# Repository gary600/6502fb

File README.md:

# 6502 Framebuffer
A 160 by 120 pixel, 256-color framebuffer and VGA generator for a 6502-based computer, made
for CMU 98-341 Build Your Own Breadboard Computer.

Heavily inspired by Ben Eater's "[world's worst video
card](https://www.youtube.com/watch?v=l7rce6IQDWs)" saga, but with many
improvements:
- better timing compliance (shorter critical path -> no vertical artifacts)
- FFs instead of latches (easier to debug timing)
- higher resolution (160x120 vs. 100x75), accomplished through memory banking
- more common VGA mode (640x480 vs. 800x600)
- double-bufferring (updates aren't restricted to blanking period)
- software blanking (show solid black or white without drawing to every pixel)
- configurability (disable NMI if not needed)

This repo contains the KiCad files for the board, a corresponding Verilog
design and testbench, and a software simulator.

The board went through 2 revisions before it worked fully:

## Rev1
Revision 1 worked well enough to generate a valid VGA signal, but I made a major
mistake on the SRAM pinout which led to it not being able to interface with the
6502 computer. Another mistake: my minimum via diameter was too small, so it
cost like $40 extra...

However, despite these faults, I was able to bodge the row and column pins to
allow it to display an image from an EEPROM.

KiCad render

KiCad board view

 Part of the arduous debugging
process that eventually led to me discovering the SRAM mistake...

 It works! (with a static image...) The
EEPROM I used here has a much slower read speed than the SRAMs I designed for,
which leads to the vertial artifacts on some pixels here.

Closeup of Rev1 bodges: SRAMs removed and row/column signals routed to EEPROM + color routed in through header

## Rev2
Revision 2 fixed the pinout of the SRAM ICs, fixed the via size issue, added a
debug header for the config register, and added an optional 5V regulator that
can be used to power the entire computer.

KiCad render

KiCad board view

Final assembled board!

Power-on noise: this is expected! The SRAM does not have a deterministic state when powered on.

Drawing to the screen works!

And it can redraw live!

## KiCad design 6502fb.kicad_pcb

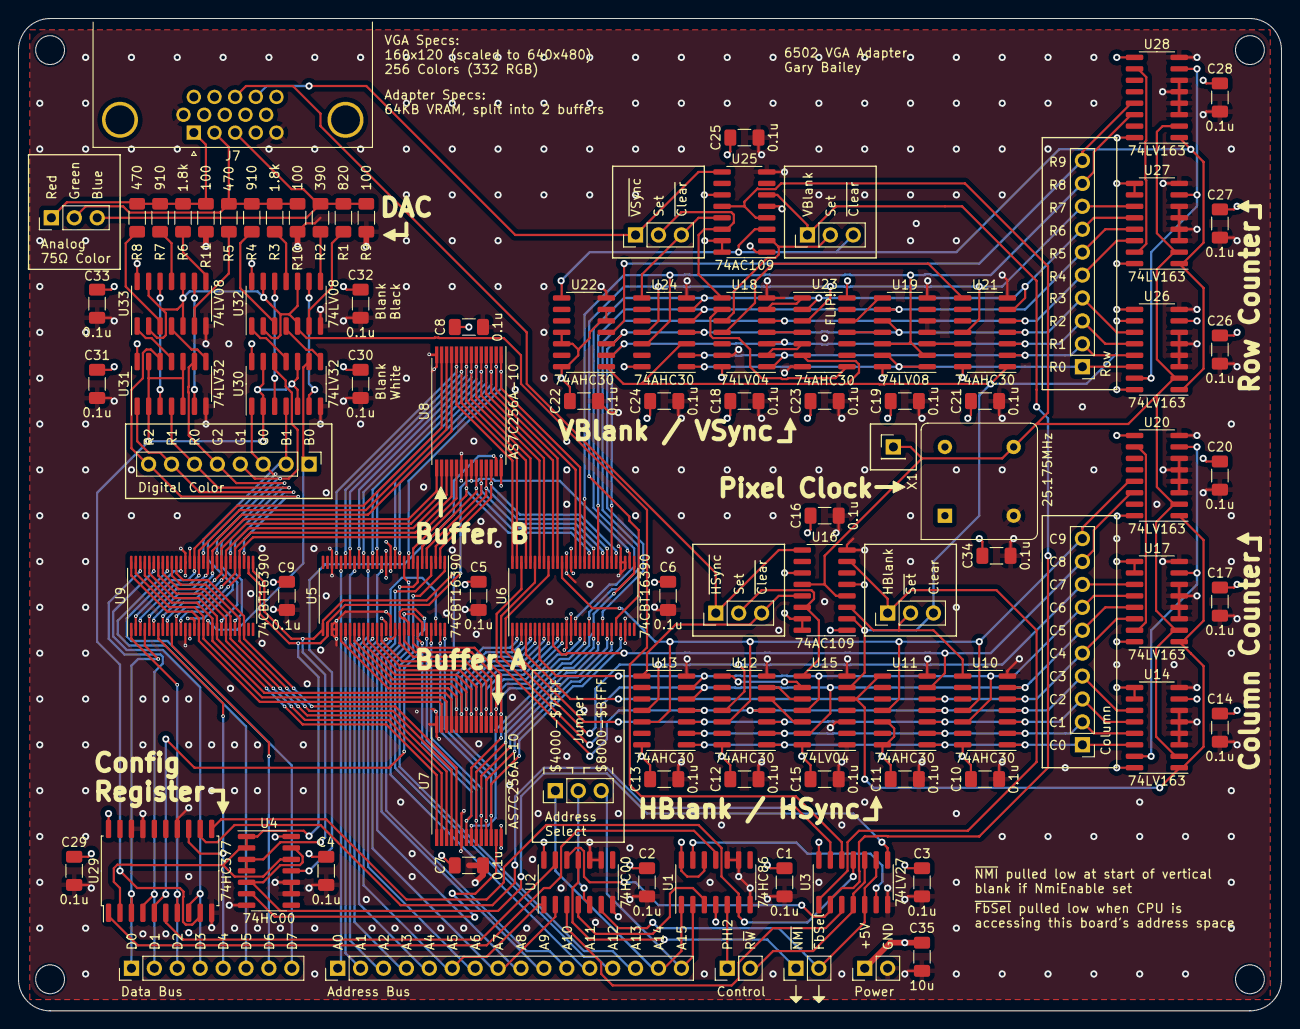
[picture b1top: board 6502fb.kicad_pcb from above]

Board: 4 copper layers, 140.0 x 110.0 mm, 100 parts (0 on the bottom side), 168 nets.

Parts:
C1, C2, C3, C4, C5, C6, C7, C8, C9, C10, C11, C12, C13, C14, C15, C16, C17, C18, C19, C20, C21, C22, C23, C24, C25, C26, C27, C28, C29, C30, C31, C32, C33, C34: 0.1u; C_1206_3216Metric_Pad1.33x1.80mm_HandSolder
C35: 10u; C_1206_3216Metric_Pad1.33x1.80mm_HandSolder
H1, H2, H3, H4: MountingHole; MountingHole_3.2mm_M3
J1, J3, J5: Conn_01x02; PinHeader_1x02_P2.54mm_Vertical
J2, J8: Conn_01x08; PinHeader_1x08_P2.54mm_Vertical
J4: Conn_01x16; PinHeader_1x16_P2.54mm_Vertical
J6, J11, J12, J13, J14, J15: Conn_01x03; PinHeader_1x03_P2.54mm_Vertical
J7: DE15_Receptacle_HighDensity; DSUB-15-HD_Female_Horizontal_P2.29x1.98mm_EdgePinOffset8.35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
J9, J10: Conn_01x10; PinHeader_1x10_P2.54mm_Vertical
J16: Conn_01x01; PinHeader_1x01_P2.54mm_Vertical
R1: 820; R_1206_3216Metric_Pad1.30x1.75mm_HandSolder
R2: 390; R_1206_3216Metric_Pad1.30x1.75mm_HandSolder
R3, R6: 1.8k; R_1206_3216Metric_Pad1.30x1.75mm_HandSolder
R4, R7: 910; R_1206_3216Metric_Pad1.30x1.75mm_HandSolder
R5, R8: 470; R_1206_3216Metric_Pad1.30x1.75mm_HandSolder
R9, R10, R11: 100; R_1206_3216Metric_Pad1.30x1.75mm_HandSolder
U1: 74HC86; SOIC-14_3.9x8.7mm_P1.27mm
U2, U4: 74HC00; SOIC-14_3.9x8.7mm_P1.27mm
U3: 74LV27; SOIC-14_3.9x8.7mm_P1.27mm
U5, U6, U9: 74CBT16390; TSSOP-56_6.1x14mm_P0.5mm
U7, U8: AS7C256A-10; TSOP-I-28_11.8x8mm_P0.55mm
U10, U11, U12, U13, U21, U22, U23, U24: 74AHC30; SOIC-14_3.9x8.7mm_P1.27mm
U14, U17, U20, U26, U27, U28: 74LV163; SOIC-16_3.9x9.9mm_P1.27mm
U15, U18: 74LV04; SOIC-14_3.9x8.7mm_P1.27mm
U16, U25: 74AC109; SOIC-16_3.9x9.9mm_P1.27mm
U19, U32, U33: 74LV08; SOIC-14_3.9x8.7mm_P1.27mm
U29: 74HC377; SOIC-20W_7.5x12.8mm_P1.27mm
U30, U31: 74LV32; SOIC-14_3.9x8.7mm_P1.27mm
X1: 25.175MHz; Oscillator_DIP-8

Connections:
+5V: C1.1, C2.1, C3.1, C4.1, C5.1, C6.1, C7.1, C8.1, C9.1, C10.1, C11.1, C12.1, C13.1, C14.1, C15.1, C16.1, C17.1, C18.1, C19.1, C20.1, C21.1, C22.1, C23.1, C24.1, C25.1, C26.1, C27.1, C28.1, C29.1, C30.1, C31.1, C32.1, C33.1, C34.1, C35.1, J3.1, U1.4, U1.12, U1.14 (VCC), U2.14 (VCC), U3.14 (VCC), U4.14 (VCC), U5.14 (V_{CC}), U5.43 (V_{CC}), U6.14 (V_{CC}), U6.43 (V_{CC}), U7.28 (VCC), U8.28 (VCC), U9.14 (V_{CC}), U9.43 (V_{CC}), U10.14 (VCC), U11.12, U11.14 (VCC), U12.14 (VCC), U13.14 (VCC), U14.7 (CEP), U14.9 (~PE), U14.10 (CET), U14.16 (VCC), U15.14 (VCC), U16.1 (~R), U16.5 (~S), U16.11 (~S), U16.15 (~R), U16.16 (VCC), U17.9 (~PE), U17.10 (CET), U17.16 (VCC), U18.14 (VCC), U19.14 (VCC), U20.9 (~PE), U20.16 (VCC), U21.14 (VCC), U22.5, U22.6, U22.11, U22.12, U22.14 (VCC), U23.14 (VCC), U24.14 (VCC), U25.1 (~R), U25.5 (~S), U25.11 (~S), U25.15 (~R), U25.16 (VCC), U26.7 (CEP), U26.9 (~PE), U26.16 (VCC), U27.9 (~PE), U27.10 (CET), U27.16 (VCC), U28.9 (~PE), U28.16 (VCC), U29.20 (VCC), U30.14 (VCC), U31.14 (VCC), U32.14 (VCC), U33.14 (VCC), X1.1 (EN), X1.8 (Vcc)
/AddrPhys14: J4.15, J6.1, U1.1
/AddrPhys15: J4.16, J6.3, U1.2
/AddrSel: J6.2, U2.5
/Blue: J7.3, J15.3, R1.2, R2.2, R9.1
/ConfigReg/BlankBlack: U3.13, U29.12 (Q4)
/ConfigReg/BlankWhite: U29.9 (Q3), U30.2, U30.5, U30.10, U30.13, U31.2, U31.5, U31.10, U31.13
/ConfigReg/DataIn0: J2.1, U9.4 (A3), U29.3 (D0)
/ConfigReg/DataIn1: J2.2, U9.54 (A2), U29.4 (D1)
/ConfigReg/DataIn2: J2.3, U9.1 (A1), U29.7 (D2)
/ConfigReg/DataIn3: J2.4, U9.51 (A4), U29.8 (D3)
/ConfigReg/DataIn4: J2.5, U9.7 (A5), U29.13 (D4)
/ConfigReg/DataIn5: J2.6, U9.48 (A6)
/ConfigReg/DataIn6: J2.7, U9.10 (A7)
/ConfigReg/DataIn7: J2.8, U9.45 (A8)
/ConfigReg/NmiEnable: U2.13, U29.6 (Q2)
/Counters/Col0: J10.1, U10.1, U11.1, U12.1, U13.1, U14.14 (Q0)
/Counters/Col1: J10.2, U10.2, U11.2, U12.2, U13.2, U14.13 (Q1)
/Counters/Col2: J10.3, U6.1 (A1), U10.3, U11.3, U12.3, U13.3, U14.12 (Q2)
/Counters/Col3: J10.4, U6.54 (A2), U10.4, U11.4, U12.4, U13.4, U14.11 (Q3)
/Counters/Col4: J10.5, U6.4 (A3), U10.5, U11.5, U17.14 (Q0)
/Counters/Col5: J10.6, U6.51 (A4), U10.6, U13.5, U15.13, U17.13 (Q1)
/Counters/Col6: J10.7, U6.7 (A5), U10.12, U13.6, U15.11, U17.12 (Q2)
/Counters/Col7: J10.8, U6.48 (A6), U12.11, U13.11, U17.11 (Q3)
/Counters/Col8: J10.9, U6.10 (A7), U11.6, U20.14 (Q0)
/Counters/Col9: J10.10, U6.45 (A8), U10.11, U11.11, U12.12, U13.12, U20.13 (Q1)
/Counters/HBlankClear: J11.3, U15.6, U16.2 (J), U21.1, U22.1, U23.6, U24.3, U26.10 (CET)
/Counters/HSyncSet: J12.2, U15.8, U16.14 (J)
/Counters/PxClock: J16.1, U14.2 (CP), U16.4 (C), U16.12 (C), U17.2 (CP), U20.2 (CP), U25.4 (C), U25.12 (C), U26.2 (CP), U27.2 (CP), U28.2 (CP), X1.5 (OUT)
/Counters/Row0: J9.1, U19.1, U19.13, U24.1, U26.14 (Q0)
/Counters/Row1: J9.2, U18.1, U21.2, U24.2, U26.13 (Q1)
/Counters/Row2: J9.3, U6.34 (A14), U18.3, U21.3, U22.2, U26.12 (Q2)
/Counters/Row3: J9.4, U6.21 (A13), U19.10, U21.4, U22.3, U24.4, U26.11 (Q3)
/Counters/Row4: J9.5, U6.18 (A11), U18.5, U21.5, U27.14 (Q0)
/Counters/Row5: J9.6, U6.37 (A12), U19.9, U24.5, U27.13 (Q1)
/Counters/Row6: J9.7, U6.15 (A9), U21.6, U23.2, U24.6, U27.12 (Q2)
/Counters/Row7: J9.8, U6.24 (A15), U21.11, U23.3, U24.11, U27.11 (Q3)
/Counters/Row8: J9.9, U6.40 (A10), U19.2, U19.12, U24.12, U28.14 (Q0)
/Counters/Row9: J9.10, U22.4, U28.13 (Q1)
/Counters/VBlankSet: J13.2, U18.10, U25.2 (J)
/Counters/VSyncSet: J14.2, U18.8, U25.14 (J)
/Counters/~Col5: U12.5, U15.12
/Counters/~Col6: U12.6, U15.10
/Counters/~HBlankClear: U11.8, U14.1 (~MR), U15.5, U17.1 (~MR), U20.1 (~MR)
/Counters/~HBlankSet: J11.2, U10.8, U16.3 (~K)
/Counters/~HSyncClear: J12.3, U13.8, U16.13 (~K)
/Counters/~Row1: U18.2, U23.5
/Counters/~Row2: U18.4, U23.4
/Counters/~Row4: U18.6, U23.1
/Counters/~VBlankClear: J13.3, U22.8, U25.3 (~K), U26.1 (~MR), U27.1 (~MR), U28.1 (~MR)
/Counters/~VSyncClear: J14.3, U24.8, U25.13 (~K)
/DAC/PixelOut0: J8.1, U9.18 (A11), U30.9
/DAC/PixelOut1: J8.2, U9.40 (A10), U30.4
/DAC/PixelOut2: J8.3, U9.15 (A9), U30.1
/DAC/PixelOut3: J8.4, U9.37 (A12), U30.12
/DAC/PixelOut4: J8.5, U9.21 (A13), U31.9
/DAC/PixelOut5: J8.6, U9.34 (A14), U31.4
/DAC/PixelOut6: J8.7, U9.24 (A15), U31.1
/DAC/PixelOut7: J8.8, U9.31 (A16), U31.12
/DAC/~BlankBlack: U3.12, U32.2, U32.5, U32.10, U32.13, U33.2, U33.5, U33.10, U33.13
/Green: J7.2, J15.2, R3.2, R4.2, R5.2, R10.1
/HBlank: J11.1, U3.1, U16.7 (~Q)
/Memory/AddrA0: U5.33 (1B15), U6.2 (2B1), U7.10 (A0)
/Memory/AddrA1: U5.35 (1B14), U6.3 (2B2), U7.9 (A1)
/Memory/AddrA2: U5.36 (1B13), U6.5 (2B3), U7.8 (A2)
/Memory/AddrA3: U5.38 (1B12), U6.6 (2B4), U7.7 (A3)
/Memory/AddrA4: U5.39 (1B11), U6.8 (2B5), U7.6 (A4)
/Memory/AddrA5: U5.41 (1B10), U6.9 (2B6), U7.5 (A5)
/Memory/AddrA6: U5.42 (1B9), U6.11 (2B7), U7.4 (A6)
/Memory/AddrA7: U5.46 (1B8), U6.12 (2B8), U7.3 (A7)
/Memory/AddrA8: U5.55 (1B2), U6.23 (2B14), U7.25 (A8)
/Memory/AddrA9: U5.53 (1B3), U6.22 (2B13), U7.24 (A9)
/Memory/AddrA10: U5.50 (1B5), U6.19 (2B11), U7.21 (A10)
/Memory/AddrA11: U5.52 (1B4), U6.20 (2B12), U7.23 (A11)
/Memory/AddrA12: U5.47 (1B7), U6.16 (2B9), U7.2 (A12)
/Memory/AddrA13: U5.56 (1B1), U6.25 (2B15), U7.26 (A13)
/Memory/AddrA14: U5.49 (1B6), U6.17 (2B10), U7.1 (A14)
/Memory/AddrB0: U5.25 (2B15), U6.56 (1B1), U8.10 (A0)
/Memory/AddrB1: U5.23 (2B14), U6.55 (1B2), U8.9 (A1)
/Memory/AddrB2: U5.22 (2B13), U6.53 (1B3), U8.8 (A2)
/Memory/AddrB3: U5.20 (2B12), U6.52 (1B4), U8.7 (A3)
/Memory/AddrB4: U5.19 (2B11), U6.50 (1B5), U8.6 (A4)
/Memory/AddrB5: U5.17 (2B10), U6.49 (1B6), U8.5 (A5)
/Memory/AddrB6: U5.16 (2B9), U6.47 (1B7), U8.4 (A6)
/Memory/AddrB7: U5.12 (2B8), U6.46 (1B8), U8.3 (A7)
/Memory/AddrB8: U5.3 (2B2), U6.35 (1B14), U8.25 (A8)
/Memory/AddrB9: U5.5 (2B3), U6.36 (1B13), U8.24 (A9)
/Memory/AddrB10: U5.8 (2B5), U6.39 (1B11), U8.21 (A10)
/Memory/AddrB11: U5.6 (2B4), U6.38 (1B12), U8.23 (A11)
/Memory/AddrB12: U5.11 (2B7), U6.42 (1B9), U8.2 (A12)
/Memory/AddrB13: U5.2 (2B1), U6.33 (1B15), U8.26 (A13)
/Memory/AddrB14: U5.9 (2B6), U6.41 (1B10), U8.1 (A14)
/Memory/AddrCPU0: J4.1, U5.24 (A15)
/Memory/AddrCPU1: J4.2, U5.34 (A14)
/Memory/AddrCPU2: J4.3, U5.21 (A13)
/Memory/AddrCPU3: J4.4, U5.37 (A12)
/Memory/AddrCPU4: J4.5, U5.18 (A11)
/Memory/AddrCPU5: J4.6, U2.1, U5.40 (A10)
/Memory/AddrCPU6: J4.7, U5.15 (A9)
/Memory/AddrCPU7: J4.8, U2.2, U5.45 (A8)
/Memory/AddrCPU8: J4.9, U5.54 (A2)
/Memory/AddrCPU9: J4.10, U5.4 (A3)
/Memory/AddrCPU10: J4.11, U5.7 (A5)
/Memory/AddrCPU11: J4.12, U5.51 (A4)
/Memory/AddrCPU12: J4.13, U5.10 (A7)
/Memory/AddrCPU13: J4.14, U5.1 (A1)
/Memory/AddrCPU14: U5.48 (A6), U29.5 (Q1)
/Memory/BufSel: U4.1, U4.2, U4.12, U5.30 (~OE1), U6.30 (~OE1), U8.22 (~OE), U9.30 (~OE1), U29.2 (Q0)
/Memory/DataA0: U7.11 (Q0), U9.19 (2B11), U9.53 (1B3)
/Memory/DataA1: U7.12 (Q1), U9.17 (2B10), U9.55 (1B2)
/Memory/DataA2: U7.13 (Q2), U9.16 (2B9), U9.56 (1B1)
/Memory/DataA3: U7.15 (Q3), U9.20 (2B12), U9.52 (1B4)
/Memory/DataA4: U7.16 (Q4), U9.22 (2B13), U9.50 (1B5)
/Memory/DataA5: U7.17 (Q5), U9.23 (2B14), U9.49 (1B6)
/Memory/DataA6: U7.18 (Q6), U9.25 (2B15), U9.47 (1B7)
/Memory/DataA7: U7.19 (Q7), U9.26 (2B16), U9.46 (1B8)
/Memory/DataB0: U8.11 (Q0), U9.5 (2B3), U9.39 (1B11)
/Memory/DataB1: U8.12 (Q1), U9.3 (2B2), U9.41 (1B10)
/Memory/DataB2: U8.13 (Q2), U9.2 (2B1), U9.42 (1B9)
/Memory/DataB3: U8.15 (Q3), U9.6 (2B4), U9.38 (1B12)
/Memory/DataB4: U8.16 (Q4), U9.8 (2B5), U9.36 (1B13)
/Memory/DataB5: U8.17 (Q5), U9.9 (2B6), U9.35 (1B14)
/Memory/DataB6: U8.18 (Q6), U9.11 (2B7), U9.33 (1B15)
/Memory/DataB7: U8.19 (Q7), U9.12 (2B8), U9.32 (1B16)
/Memory/~BufSel: U4.3, U4.4, U5.29 (~OE2), U6.29 (~OE2), U7.22 (~OE), U9.29 (~OE2)
/Memory/~WeA: U4.6, U7.27 (~WE)
/Memory/~WeB: U4.11, U8.27 (~WE)
/Phi2: J1.1, U1.5
/Red: J7.1, J15.1, R6.2, R7.2, R8.2, R11.1
/R~W: J1.2, U3.4, U3.10
/VBlank: J13.1, U2.12, U3.2, U25.6 (Q)
/WriteMem: U3.8, U4.5, U4.13
/~FbSel: J5.2, U2.6, U3.5, U3.9
/~HSync: J7.13, J12.1, U16.9 (~Q)
/~NMI: J5.1, U2.11
/~Phi2: U1.6, U3.11, U29.11 (CP)
/~RegSel: U2.3, U3.3
/~VSync: J7.14, J14.1, U25.9 (~Q)
/~WriteReg: U1.11, U29.1 (~E)
GND: C1.2, C2.2, C3.2, C4.2, C5.2, C6.2, C7.2, C8.2, C9.2, C10.2, C11.2, C12.2, C13.2, C14.2, C15.2, C16.2, C17.2, C18.2, C19.2, C20.2, C21.2, C22.2, C23.2, C24.2, C25.2, C26.2, C27.2, C28.2, C29.2, C30.2, C31.2, C32.2, C33.2, C34.2, C35.2, J3.2, J7.5, J7.6, J7.7, J7.8, J7.10, R9.2, R10.2, R11.2, U1.7 (GND), U1.9, U1.10, U2.7 (GND), U2.9, U2.10, U3.7 (GND), U4.7 (GND), U4.9, U4.10, U5.13 (GND), U5.26 (2B16), U5.31 (A16), U5.32 (1B16), U5.44 (GND), U6.13 (GND), U6.26 (2B16), U6.31 (A16), U6.32 (1B16), U6.44 (GND), U7.14 (GND), U7.20 (~CS), U8.14 (GND), U8.20 (~CS), U9.13 (GND), U9.44 (GND), U10.7 (GND), U11.7 (GND), U12.7 (GND), U13.7 (GND), U14.3 (D0), U14.4 (D1), U14.5 (D2), U14.6 (D3), U14.8 (GND), U15.1, U15.3, U15.7 (GND), U16.8 (GND), U17.3 (D0), U17.4 (D1), U17.5 (D2), U17.6 (D3), U17.8 (GND), U18.7 (GND), U18.13, U19.4, U19.5, U19.7 (GND), U20.3 (D0), U20.4 (D1), U20.5 (D2), U20.6 (D3), U20.8 (GND), U21.7 (GND), U22.7 (GND), U23.7 (GND), U24.7 (GND), U25.8 (GND), U26.3 (D0), U26.4 (D1), U26.5 (D2), U26.6 (D3), U26.8 (GND), U27.3 (D0), U27.4 (D1), U27.5 (D2), U27.6 (D3), U27.8 (GND), U28.3 (D0), U28.4 (D1), U28.5 (D2), U28.6 (D3), U28.8 (GND), U29.10 (GND), U29.14 (D5), U29.17 (D6), U29.18 (D7), U30.7 (GND), U31.7 (GND), U32.7 (GND), U33.7 (GND), X1.4 (GND)
unnamed: R1.1, U32.6
unnamed: R2.1, U32.8
unnamed: R3.1, U32.11
unnamed: R4.1, U32.3
unnamed: R5.1, U33.6
unnamed: R6.1, U33.8
unnamed: R7.1, U33.11
unnamed: R8.1, U33.3
unnamed: U1.3, U2.4
unnamed: U1.13, U3.6
unnamed: U12.8, U15.9
unnamed: U14.15 (TC), U17.7 (CEP), U20.7 (CEP)
unnamed: U17.15 (TC), U20.10 (CET)
unnamed: U18.9, U23.8
unnamed: U18.11, U21.8
unnamed: U19.3, U21.12
unnamed: U19.8, U23.12
unnamed: U19.11, U23.11
unnamed: U26.15 (TC), U27.7 (CEP), U28.7 (CEP)
unnamed: U27.15 (TC), U28.10 (CET)
unnamed: U30.3, U32.12
unnamed: U30.6, U32.9
unnamed: U30.8, U32.4
unnamed: U30.11, U32.1
unnamed: U31.3, U33.12
unnamed: U31.6, U33.9
unnamed: U31.8, U33.4
unnamed: U31.11, U33.1

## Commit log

2023-10-18 initial commit (~2 weeks of work)
2023-10-19 cleanup
2023-10-23 remove 3390, cleanup
2023-10-29 work on DAC
2023-10-29 work on main page layout
2023-10-29 finish control logic?
2023-11-02 Add verilog model
2023-11-02 Update verilog model
2023-11-02 misc fixes, start on pcb
2023-11-02 fix and update verilog model
2023-11-02 start working on timing sim
2023-11-04 more component-level simulation
2023-11-04 finish timing
2023-11-04 Fix some timing, simulate writing to memory
2023-11-05 Work on layout/routing
2023-11-05 More routing work
2023-11-07 pcb organization
2023-11-07 Suuuper dense routing for column counter
2023-11-07 Row counter logic
2023-11-08 Routing work
2023-11-08 Memory routing *screams*
2023-11-08 MOOORE memory routing
2023-11-09 more layout
2023-11-10 layout continues...
2023-11-11 finalize board layout at 140x110mm
2023-11-11 almost done wiring...
2023-11-12 Done routing!!
2023-11-13 Make DRC quiet, add loooots of vias
2023-11-13 Add fp-info-cache to gitignore
2023-11-13 Test exporting
2023-11-13 Rename project to 6502fb
2023-11-14 Add careers
2023-11-14 More careers and pretty text
2023-11-14 FINAL CHANGES FOR REV1
2023-11-17 add software emulator (yoinked from carson)
2023-11-18 fix colors for rendering
2023-11-18 Simulator debugging
2023-11-18 Run event loop on main thread to prevent crash
2023-11-18 Convert fbconfig to bitfield
2023-11-21 Start on library
2023-12-05 Add outputs for vga simulator
2023-12-05 begin rev 2... more routing :(
2023-12-05 fix HC377 package
2023-12-19 Rev2 work
2023-12-19 rev2 mostly done now
2023-12-20 fix VGA plug footprint
2024-01-07 add caps for 7805
2024-01-07 rev 2 final version gerbers
2024-11-27 Readme w/ basic project writeup
